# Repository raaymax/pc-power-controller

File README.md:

# ATX controller

Connect your PC to your Home Assistant instance.

## MIT License

Copyright (c) 2025 Mateusz Russak

Permission is hereby granted, free of charge, to any person obtaining a copy
of this software and associated documentation files (the "Software"), to deal
in the Software without restriction, including without limitation the rights  
to use, copy, modify, merge, publish, distribute, sublicense, and/or sell  
copies of the Software, and to permit persons to whom the Software is  
furnished to do so, subject to the following conditions:

The above copyright notice and this permission notice shall be included in  
all copies or substantial portions of the Software.

THE SOFTWARE IS PROVIDED "AS IS", WITHOUT WARRANTY OF ANY KIND, EXPRESS OR  
IMPLIED, INCLUDING BUT NOT LIMITED TO THE WARRANTIES OF MERCHANTABILITY,  
FITNESS FOR A PARTICULAR PURPOSE AND NONINFRINGEMENT. IN NO EVENT SHALL THE  
AUTHORS OR COPYRIGHT HOLDERS BE LIABLE FOR ANY CLAIM, DAMAGES OR OTHER  
LIABILITY, WHETHER IN AN ACTION OF CONTRACT, TORT OR OTHERWISE, ARISING FROM,  
OUT OF OR IN CONNECTION WITH THE SOFTWARE OR THE USE OR OTHER DEALINGS IN  
THE SOFTWARE.

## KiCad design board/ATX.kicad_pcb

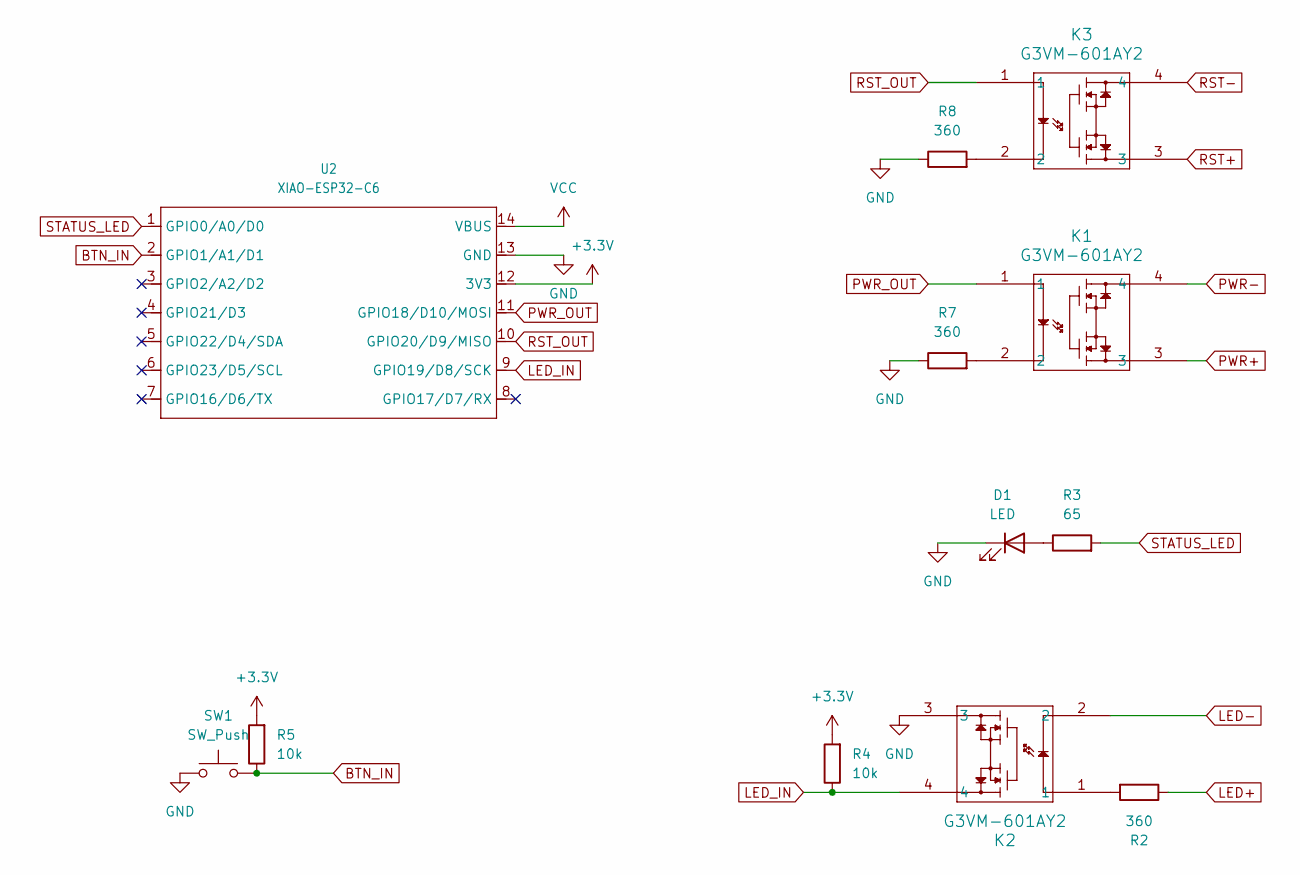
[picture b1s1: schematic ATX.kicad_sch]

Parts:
D1: LED; R_1210_3225Metric_Pad1.30x2.65mm_HandSolder
K1, K2, K3: G3VM-601AY2; A-DIP4_THD_OMR
R2, R7, R8: 360; R_0805_2012Metric_Pad1.20x1.40mm_HandSolder
R3: 65; R_0805_2012Metric_Pad1.20x1.40mm_HandSolder
R4, R5: 10k; R_0805_2012Metric_Pad1.20x1.40mm_HandSolder
SW1: SW_Push; SW_PUSH_6mm
U2: XIAO-ESP32-C6; XIAO-ESP32C6-DIP

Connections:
+3.3V: R4.2, R5.2, U2.12 (3V3)
BTN_IN: R5.1, SW1.2, U2.2 (GPIO1/A1/D1)
GND: D1.1 (K), K2.3, R7.1, R8.1, SW1.1, U2.13 (GND); also elsewhere on the board
LED+: R2.1; also elsewhere on the board
LED-: K2.2; also elsewhere on the board
LED_IN: K2.4, R4.1, U2.9 (GPIO19/D8/SCK)
unnamed: D1.2 (A), R3.1
unnamed: K1.2, R7.2
unnamed: K2.1, R2.2
unnamed: K3.2, R8.2
PWR+: K1.3; also elsewhere on the board
PWR-: K1.4; also elsewhere on the board
PWR_OUT: K1.1, U2.11 (GPIO18/D10/MOSI)
RST+: K3.3; also elsewhere on the board
RST-: K3.4; also elsewhere on the board
RST_OUT: K3.1, U2.10 (GPIO20/D9/MISO)
STATUS_LED: R3.2, U2.1 (GPIO0/A0/D0)
VCC: U2.14 (VBUS); also elsewhere on the board

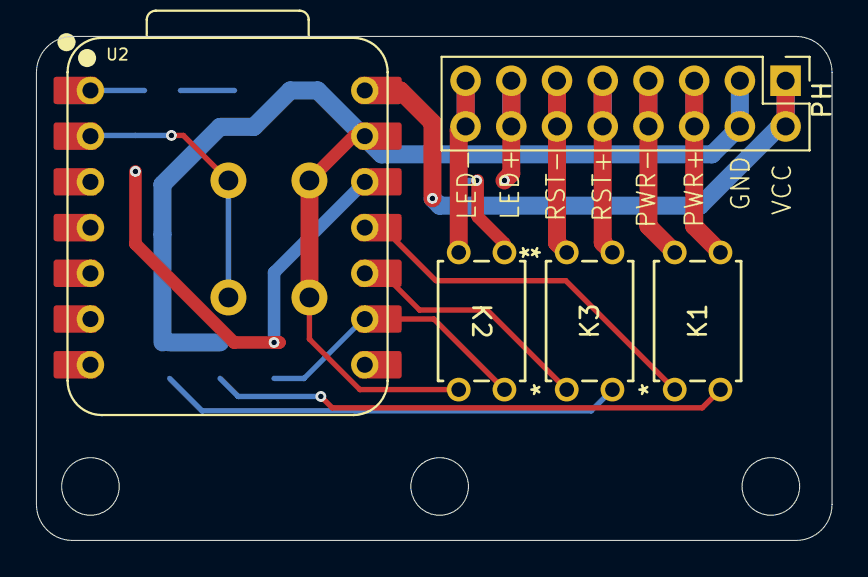
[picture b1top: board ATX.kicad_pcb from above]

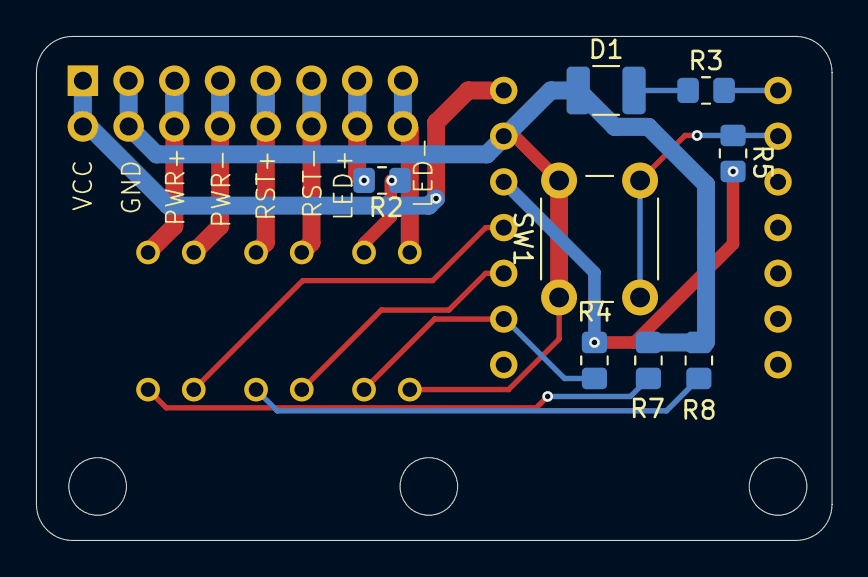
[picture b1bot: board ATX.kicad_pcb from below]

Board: 2 copper layers, 44.2 x 28.0 mm, 13 parts (8 on the bottom side), 18 nets.

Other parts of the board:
PH: PinHeader_2x08_P2.54mm_Vertical

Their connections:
GND: PH.3, PH.4; also elsewhere on the board
LED+: PH.13, PH.14; also elsewhere on the board
LED-: PH.15, PH.16; also elsewhere on the board
PWR+: PH.5, PH.6; also elsewhere on the board
PWR-: PH.7, PH.8; also elsewhere on the board
RST+: PH.9, PH.10; also elsewhere on the board
RST-: PH.11, PH.12; also elsewhere on the board
VCC: PH.1, PH.2; also elsewhere on the board

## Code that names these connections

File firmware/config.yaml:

# Basic configuration for an ESP32 device
esphome:
  name: melchior-atx
  friendly_name: Melchior ATX 

# Hardware configuration
esp32:
  board: seeed_xiao_esp32c6
  framework:
    type: esp-idf

# Enable Home Assistant API
api:

network:
  enable_ipv6: true

# Enable over-the-air updates
ota:
  platform: esphome

# If you want Wifi then uncoment this and create secrets.yaml with wifi_ssid and wifi_password
#wifi:
#  ssid: !secret wifi_ssid
#  password: !secret wifi_password

#web_server:
#  port: 80

openthread:
  tlv: !secret openthread_tlv 

output:
  - platform: gpio
    pin: GPIO18
    id: pwr_out 
    inverted: false
  - platform: gpio
    pin: GPIO20
    id: rst_out 
    inverted: false
  - platform: gpio
    pin: GPIO0
    id: status_out 
    inverted: false

button:
  - platform: output
    name: "Power Button"
    output: pwr_out
    duration: 500ms
    on_press:
      then:
        - output.turn_on: status_out
        - delay: 500ms
        - output.turn_off: status_out
  - platform: output
    name: "Power Button - Long Press"
    output: pwr_out
    duration: 5000ms
    on_press:
      then:
        - output.turn_on: status_out
        - delay: 5000ms
        - output.turn_off: status_out
  - platform: output
    name: "Reset Button"
    output: rst_out
    duration: 500ms
    on_press:
      then:
        - output.turn_on: status_out
        - delay: 100ms
        - output.turn_off: status_out
        - delay: 100ms
        - output.turn_on: status_out
        - delay: 100ms
        - output.turn_off: status_out

binary_sensor:
  - platform: gpio
    pin:
      number: GPIO19
      mode:
        input: true
        inverted: true
    name: "Power"
  - platform: gpio
    pin:
      number: GPIO21
      mode:
        input: true
        inverted: true
    name: "Button"

light:
  - platform: status_led
    name: "Status LED"
    output: status_out

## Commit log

2025-08-08 feat: pc power controller
2025-08-08 chore: licence
